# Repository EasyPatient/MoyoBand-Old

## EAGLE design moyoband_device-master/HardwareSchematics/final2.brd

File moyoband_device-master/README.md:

# Moyoband device
This repository is focused on hardware part of Moyoband project.

## Assumptions 
Our biggest goal is make a small band using nRF52840 SoC. We're going to use Bluetooth Low Energy (BLE) connection. A few bands should connect sequentially to one Raspberry Pi Zero and send data to it. We'are going to measure heart rate, saturation and temperature. To identify band, we use MAC address sent with RFID 13,56MHz.  
It's possible to add accelerometer in future, to provide better care of patient.

## Used protocols
- TWI (I2C) - connection with sensor
- BLE - wireless connection with Raspberry
- RFID - adding band to database

## Used elements
- nRF52840 Dongle and Development Kit - To provide easier debug of the code [nRF52840 DK](https://www.nordicsemi.com/Software-and-Tools/Development-Kits/nRF52840-DK)
- MAXREFDES117# I2C, Ultra Low-Energy Heart Rate and Pulse-Oximetry sensor [PRODUCENT SITE](https://www.maximintegrated.com/en/design/reference-design-center/system-board/6300.html)
- Raspberry Pi 4 - Used as server [PRODUCENT SITE](https://www.raspberrypi.org/products/raspberry-pi-4-model-b/)
- Raspberry Pi Zero W - Used as access points, bridges between BLE and Wi-Fi connection [PRODUCENT SITE](https://www.raspberrypi.org/products/raspberry-pi-zero-w/)
- PN532 RFID module - Used to read NFC data from devices and easy add them to rooms [PN532](https://botland.com.pl/moduly-i-tagi-rfid/8240-modul-rfidnfc-pn532-1356mhz-i2cspi-karta-i-brelok.html)
- Custom PCB designed by Mateusz Kozyra [Git](https://gitlab.com/MatKozyra52)

## Concept
### How should it looks like?

### Network schematics

### Hardware schematics

## Possibilities to continue work
This project is very flexible if you want to develop it. My thoughts:
1. Microcontroller
    - We should consider if we really need nRF52840 with all it's power. The core of this processor is Cortex-M4 but with all Nordic features it can be overkill.
    - Nordic's products are difficult to learn. I achieved 6mA average current consumption. In Idle_state it was about 5mA with 15mA peaks for measurment and send every 10 seconds. I think it's definitely too much. If we want to work with 100mAh battery about 170h   we need to acheive about 600uA average current.
    - Additionally cost of Nordic components is really high
    - As an alternative we can use ATmega328p or STM32 maybe
2. Connectivity
    - BLE can be really Low Power but it's difficult to configure it well. The next problem is 2.4GHz working frequency. In the same band we can find smartphones, smartwatches etc. so when we have ~70 patients on one floor we can have problems with lost connections.
    - I'm thinking about 868MHz Radio Transmission. It's much cheaper, band is not so full and it offers much better range. About current consumption it takes little more in peak but it's much shorter so probably we can optimize it.
3. Sensor
    - Algorithm is definitely not so precisious. We should provide much better error correction.
    - In future we can try to use better voltage converters to cut some current.

## Connected repos
To use this system you should downlad and configure [Moyoband Network](https://gitlab.com/moyoband-group/moyoband_network/-/tree/radoslaw_srv)
## Video
[Youtube presentation in polish](https://youtu.be/xFIGcQSHniY)
## To-Do list
- [x] Provide git repo (completed if repo is accepted by leader)
    - [x] Make concept graph
    - [x] Make repo
    - [x] Share link with course leader
- [x] Sensor handling
    - [x] Run sensor with Nordic board
    - [x] Get first data from sensor
    - [x] Calculate correct data
- [x] BLE connection
    - [x] Read about BLE stack
    - [x] Configure Development Kit for our use case
    - [x] Wake up device with internal timer
    - [x] Provide connection with NRF Connect destkop app
    - [x] Write python app to receive data from one device
    - [x] Develop app to read data sequentially
        - We're not limited in bands now
    - [x] Add comments to BLE library
- [x] RFID
    - [x] Read about getting MAC in Nordic Software Development Kit (SDK)
    - [x] Get MAC while running device
    - [x] Turn on RFID permanently
    - [x] Read data with phone
    - [x] Write python app on Raspberry to get MAC
        - It's in moyoband_network project
    - [x] Is it possible to interrupt device with RFID?
        - [x] If yes, do it
            - It's built into nRF so I did. But in library for pn532 there's bug somewhere which I can't find...
        - [x] If not, look for low energy solution
            - I consider if BLE is good way. Maybe it's better to use simple Radio transmitter without connection?
- [x] Connection with database
    - [x] Write client app
        - [x] Get list of bands from server
        - [x] Connect to bands sequentially
        - [x] Send data to server
        - [x] Provide run without ran server
            - I decided to don't do it because of security. Data could may have been stolen with any server
    - [x] Write server app
        - [x] Send bands to specified clients
        - [x] Receive and sort data from one client
        - [x] Upgrade it to work with many clients (select function!)
            - It's moyoband_network project. Actually i limited it to 5 Raspberries
        - [x] Make endpoints for app team

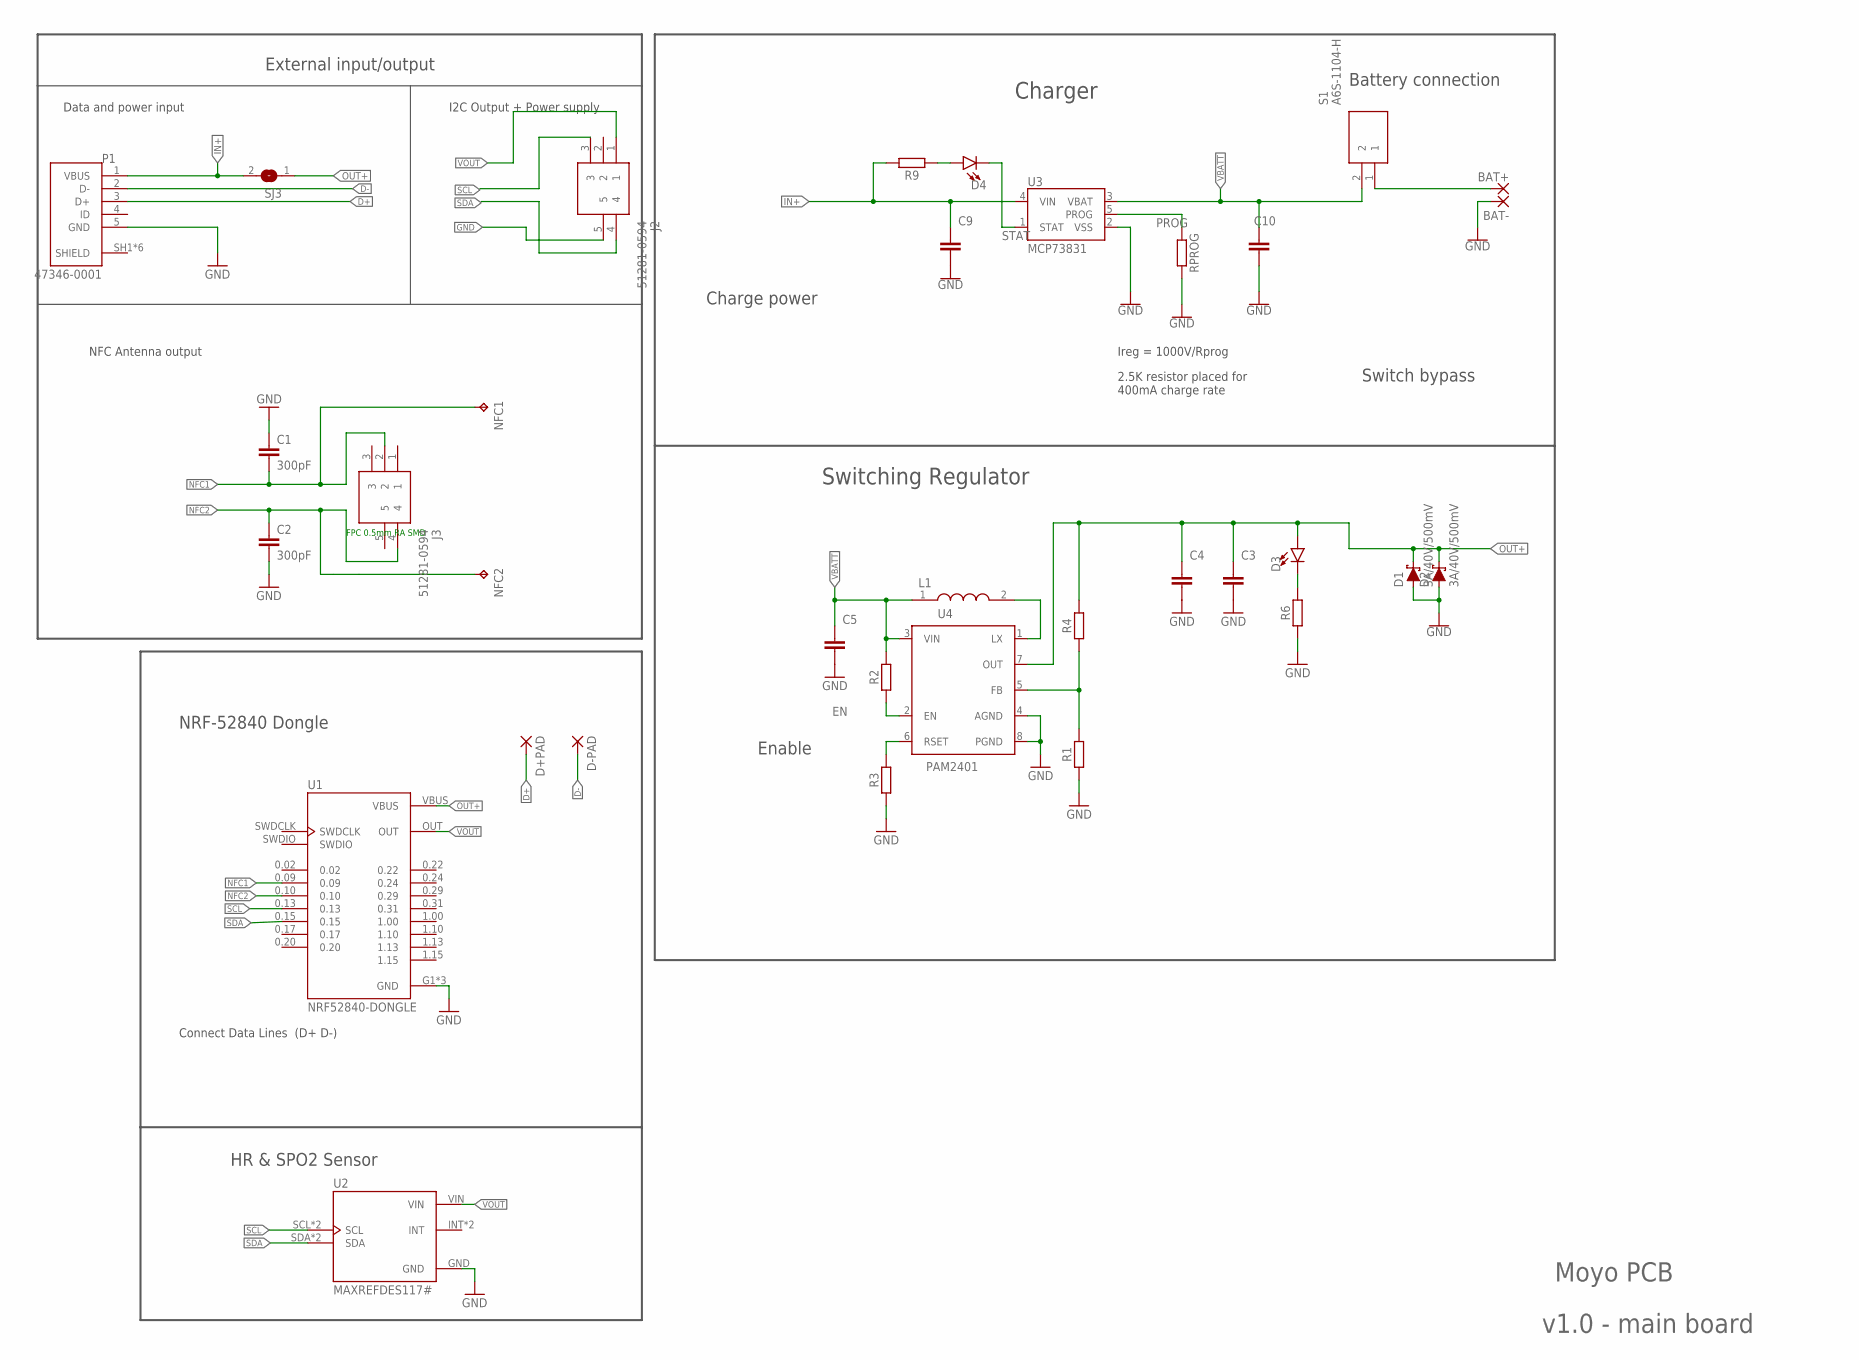
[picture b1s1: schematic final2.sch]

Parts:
BAT+: SMD5; SMD2,54-5,08
BAT-: SMD5; SMD2,54-5,08
C1, C2: 300pF; C0805
C3, C4, C5: 22uF; C0805
C9, C10: 4.7uF; C0805
D1, D2: 3A/40V/500mV; SMA-DIODE
D3: RED; CHIP-LED0805
D4: BLUE; CHIP-LED0805
D+PAD: SMD5; SMD2,54-5,08
D-PAD: SMD5; SMD2,54-5,08
J2, J3: 51281-0594
L1: 74437324022; WE-LHMI_402048
NFC1, NFC2: TPB1,27; B1,27
P1: 47346-0001; MOLEX_47346-0001
R1: 68k; M0805
R2: 750K; M0805
R3: DNP; M0805
R4: 470k; M0805
R6: 4.7k; M0805
R9: 1k; M0805
RPROG: 2.5k; M0805
S1: A6S-1104-H
SJ3: SJ
U1: NRF52840-DONGLE; MODULE_NRF52840-DONGLE
U2: MAXREFDES117#; MODULE_MAXREFDES117#
U3: MCP73831; SOT23-5
U4: PAM2401; MSOP8

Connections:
D+: D+PAD.1, P1.3 (D+)
D-: D-PAD.1, P1.2 (D-)
EN: R2.1, U4.2 (EN)
GND: BAT-.1, C1.1, C2.2, C3.2, C4.2, C5.2, C9.2, C10.2, D1.A, D2.A, J2.5, P1.5 (GND), R1.1, R3.1, R6.1, RPROG.2, U1.G1 (GND), U1.G2 (GND), U1.G3 (GND), U2.GND, U3.2 (VSS), U4.4 (AGND), U4.8 (PGND)
IN+: C9.1, P1.1 (VBUS), R9.2, SJ3.2, U3.4 (VIN)
unnamed: D3.C, R6.2
unnamed: L1.2, U4.1 (LX)
unnamed: D4.A, R9.1
unnamed: R3.2, U4.6 (RSET)
unnamed: BAT+.1, S1.1
unnamed: R1.2, R4.1, U4.5 (FB)
NFC1: C1.2, J3.2, NFC1.TP, U1.0.09
NFC2: C2.1, J3.4, NFC2.TP, U1.0.10
OUT+: C3.1, C4.1, D1.C, D2.C, D3.A, R4.2, SJ3.1, U1.VBUS, U4.7 (OUT)
PROG: RPROG.1, U3.5 (PROG)
SCL: J2.3, U1.0.13, U2.SCL, U2.SCL1 (SCL)
SDA: J2.4, U1.0.15, U2.SDA, U2.SDA1 (SDA)
STAT: D4.C, U3.1 (STAT)
VBATT: C5.1, C10.1, L1.1, R2.2, S1.2, U3.3 (VBAT), U4.3 (VIN)
VOUT: J2.1, U1.OUT, U2.VIN

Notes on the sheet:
FPC 0.5mm RA SMD
Charger
Switching Regulator
2.5K resistor placed for 400mA charge rate
Ireg = 1000V/Rprog
Enable
Charge power
Battery connection
Switch bypass
HR & SPO2 Sensor
NRF-52840 Dongle
Connect Data Lines (D+ D-)
Data and power input
NFC Antenna output
I2C Output + Power supply
External input/output
Moyo PCB
v1.0 - main board

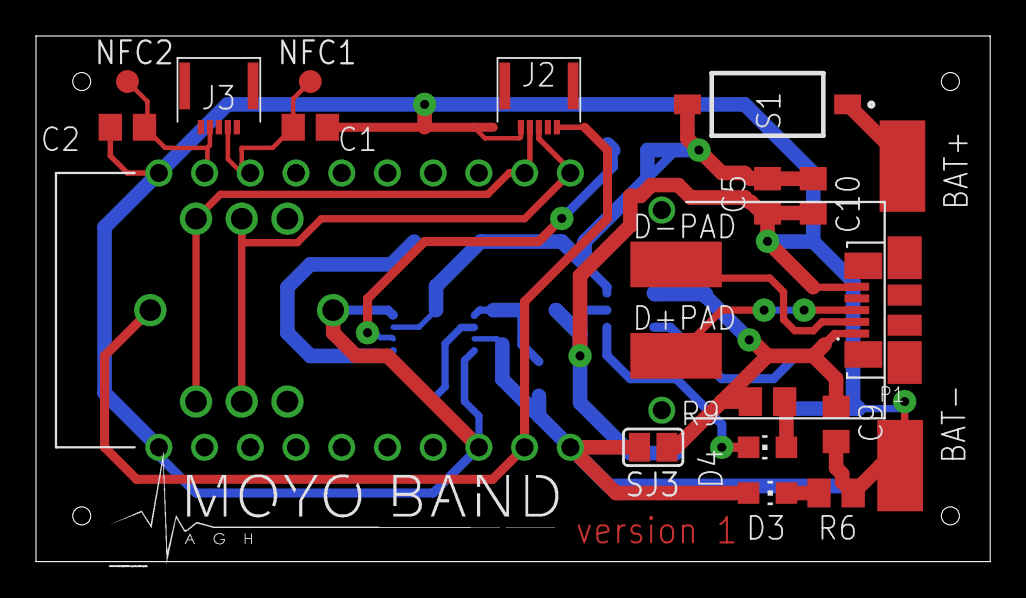
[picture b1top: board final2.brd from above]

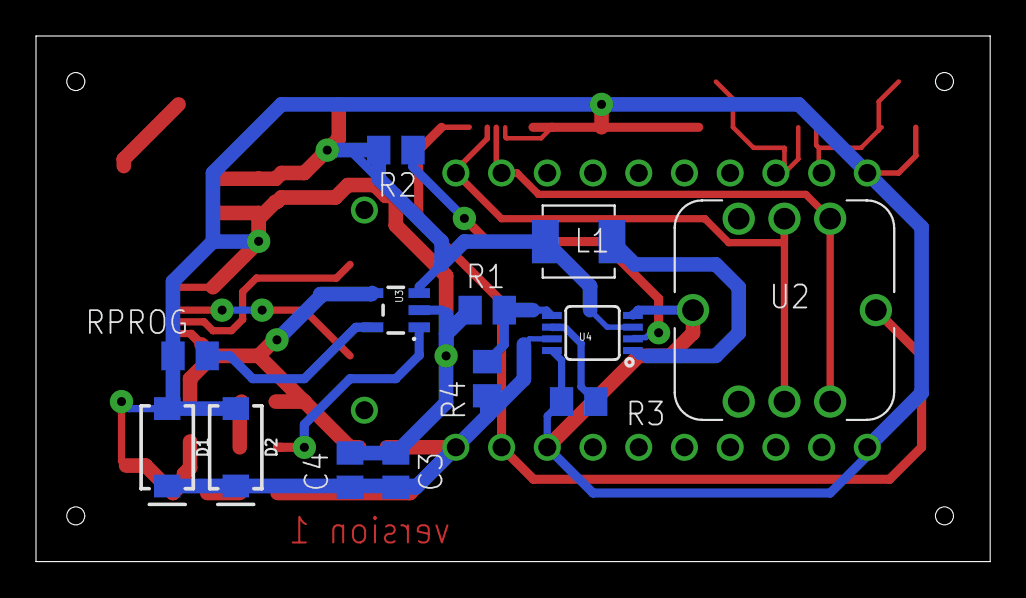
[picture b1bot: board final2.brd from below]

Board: 2 copper layers, 53.0 x 29.2 mm, 34 parts (13 on the bottom side), 20 nets.

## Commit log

2021-10-16 Transfer from gitlab to github

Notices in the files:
parts and their libraries:
SparkFun-DiscreteSemi: Licensing: Creative Commons ShareAlike 4.0 International - https://creativecommons.org/licenses/by-sa/4.0
